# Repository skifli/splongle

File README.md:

# splongle

- [splongle](#splongle)
  - [Schematic](#schematic)
  - [PCB](#pcb)
  - [BOM](#bom)

A dongle for my [split ergonomic keyboard](https://github.com/skifli/splad). It connects to the device via a USB C port at the top of the case, and there is also a reset button on the left. It will show stats like typing speed, etc, for my keyboard, while also connecting my two keyboard halves together and then to the computer via the aforementioned USB-C.

## Schematic

## PCB

## BOM

| Item                                               | Price (GBP) |
| -------------------------------------------------- | ----------- |
| 2.8" ILI9341 display                               | £6.25       |
| 3×3 mm fridge magnets (for the two case halves)    | £2.71       |
| 1×3 pin, 50 pcs (for Nice!Nano 3-pin part for PCB) | £0.92       |
| Nice!Nano clone                                    | £3.33       |
| **Total**                                          | **£13.21**  |

**Total in USD:** $17.80

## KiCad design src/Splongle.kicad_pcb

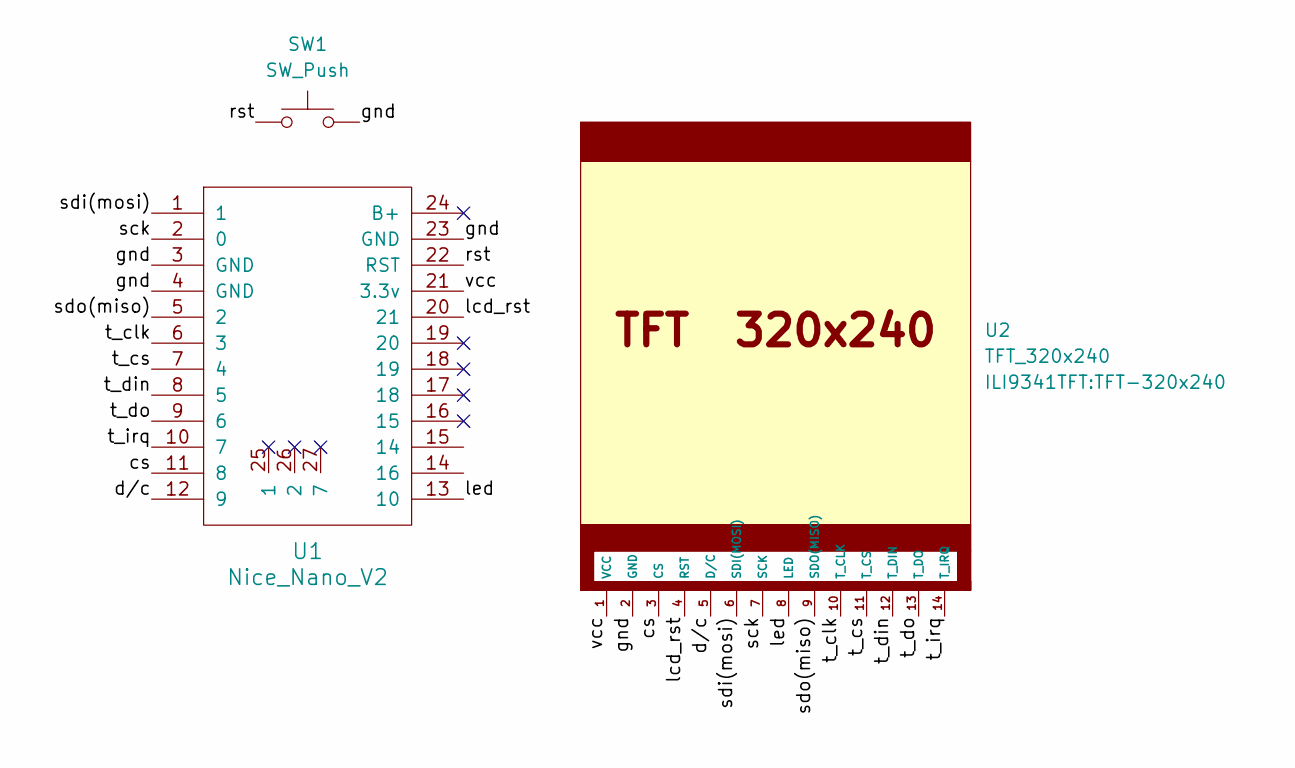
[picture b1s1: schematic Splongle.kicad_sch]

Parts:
SW1: SW_Push; Generic 2 Pin Horizontal
U1: Nice_Nano_V2
U2: TFT_320x240; TFT-320x240

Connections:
/cs: U1.11 (8), U2.3 (CS)
/d/c: U1.12 (9), U2.5 (D/C)
/gnd: SW1.2, U1.3 (GND), U1.4 (GND), U1.23 (GND), U2.2 (GND)
/lcd_rst: U1.20 (21), U2.4 (RST)
/led: U1.13 (10), U2.8 (LED)
/rst: SW1.1, U1.22 (RST)
/sck: U1.2 (0), U2.7 (SCK)
/sdi(mosi): U1.1, U2.6 (SDI(MOSI))
/sdo(miso): U1.5 (2), U2.9 (SDO(MISO))
/t_clk: U1.6 (3), U2.10 (T_CLK)
/t_cs: U1.7 (4), U2.11 (T_CS)
/t_din: U1.8 (5), U2.12 (T_DIN)
/t_do: U1.9 (6), U2.13 (T_DO)
/t_irq: U1.10 (7), U2.14 (T_IRQ)
/vcc: U1.21 (3.3v), U2.1 (VCC)

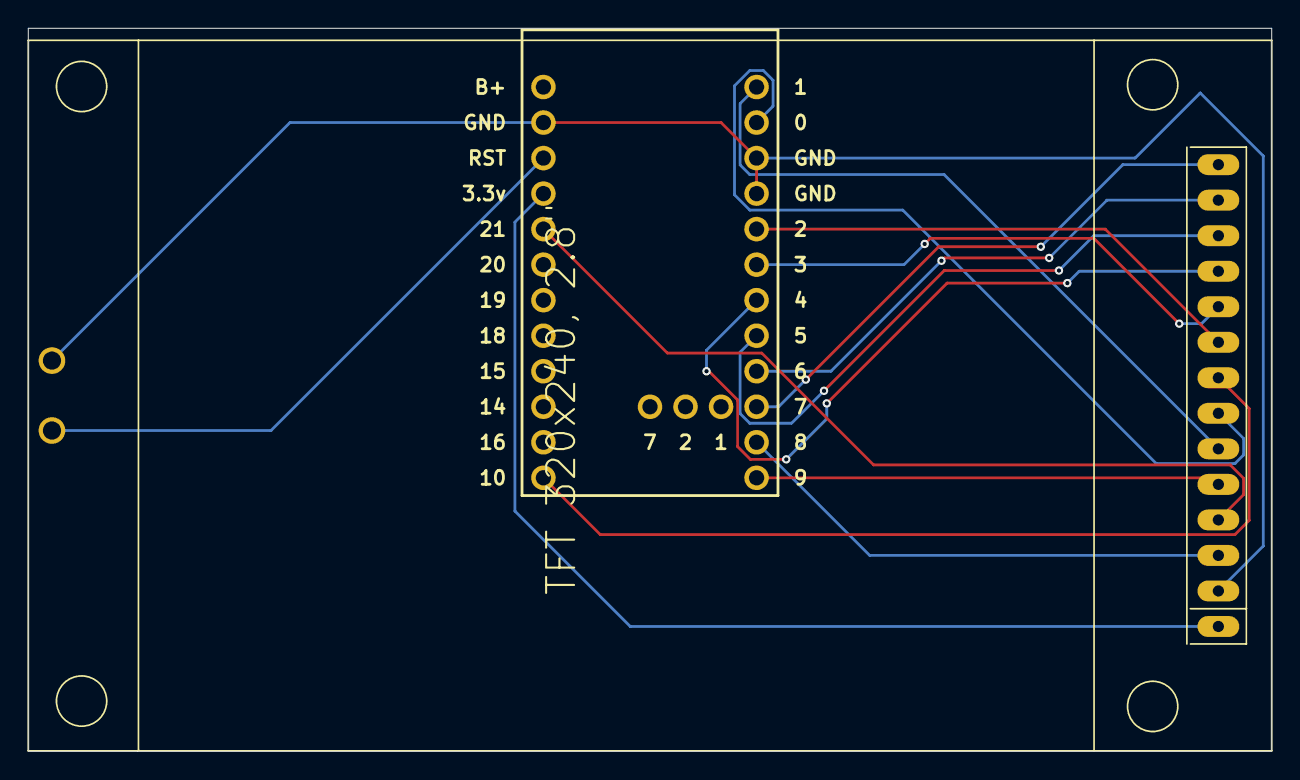
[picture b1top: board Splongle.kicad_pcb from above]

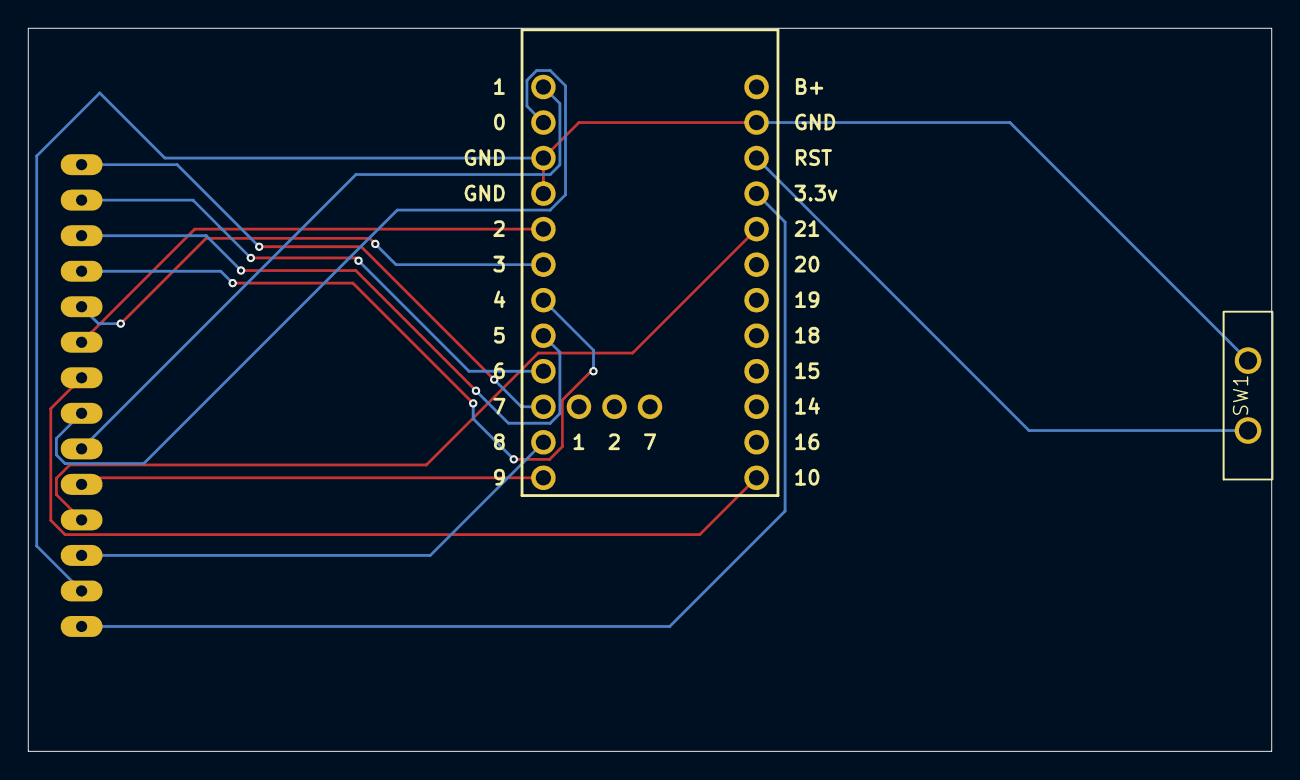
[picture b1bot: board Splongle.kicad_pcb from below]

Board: 2 copper layers, 88.9 x 51.7 mm, 3 parts (2 on the bottom side), 15 nets.

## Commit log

2025-09-20 feat: push local changes
2025-09-20 fix: wrong img path
2025-09-20 feat: update description
